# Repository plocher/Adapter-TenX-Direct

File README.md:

# Adapter-TenX-Direct
## License: Creative Commons Attribution-NonCommercial-ShareAlike

Experimental unbuffered I/O expansion board adapter for MRCS cpNode evolution

initial version

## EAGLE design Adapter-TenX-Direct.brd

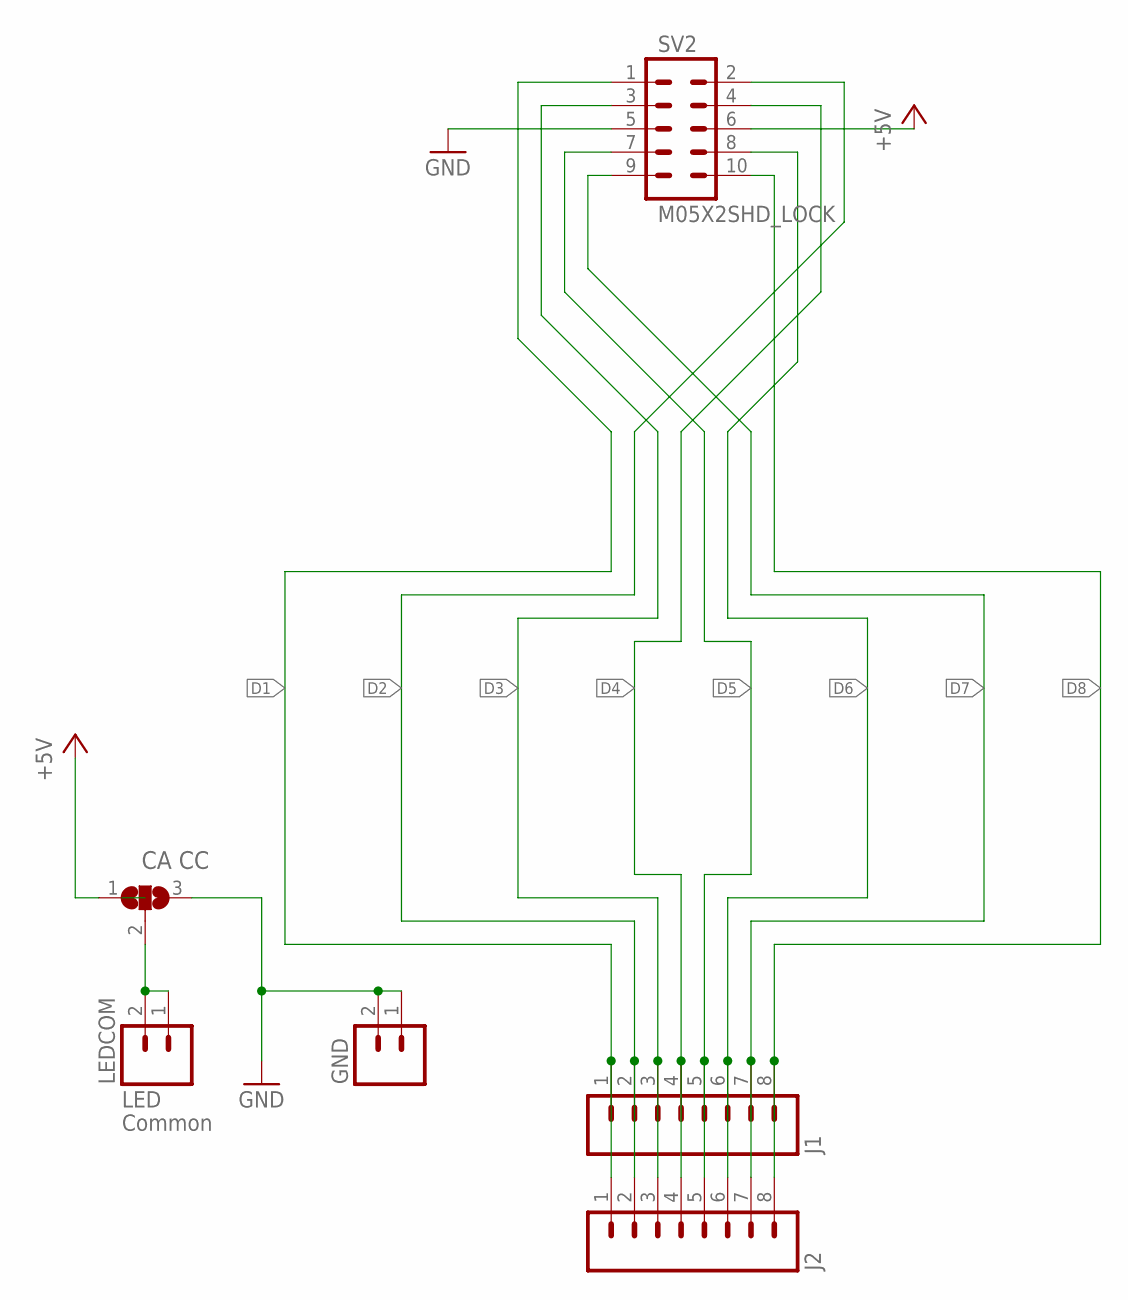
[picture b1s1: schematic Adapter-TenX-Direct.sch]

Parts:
GND: M02POLAR_LOCK; MOLEX-1X2_LOCK
J1: CONNECTOR-M08LOCK_LONGPADS; 1X08_LOCK_LONGPADS
J2: CONNECTOR-M081.56-M; KK-156-8-M
LEDCOM: M02POLAR_LOCK; MOLEX-1X2_LOCK
P1: CA CC; 3P-SMD-2X4.8
SV2: M05X2SHD_LOCK; 2X5-SHROUDED_LOCK

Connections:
+5V: P1.1, SV2.6
D1: J1.1, J2.1, SV2.1
D2: J1.2, J2.2, SV2.2
D3: J1.3, J2.3, SV2.3
D4: J1.4, J2.4, SV2.4
D5: J1.5, J2.5, SV2.7
D6: J1.6, J2.6, SV2.8
D7: J1.7, J2.7, SV2.9
D8: J1.8, J2.8, SV2.10
GND: GND.1, GND.2, P1.3, SV2.5
unnamed: LEDCOM.1, LEDCOM.2, P1.2

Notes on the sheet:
LED
Common

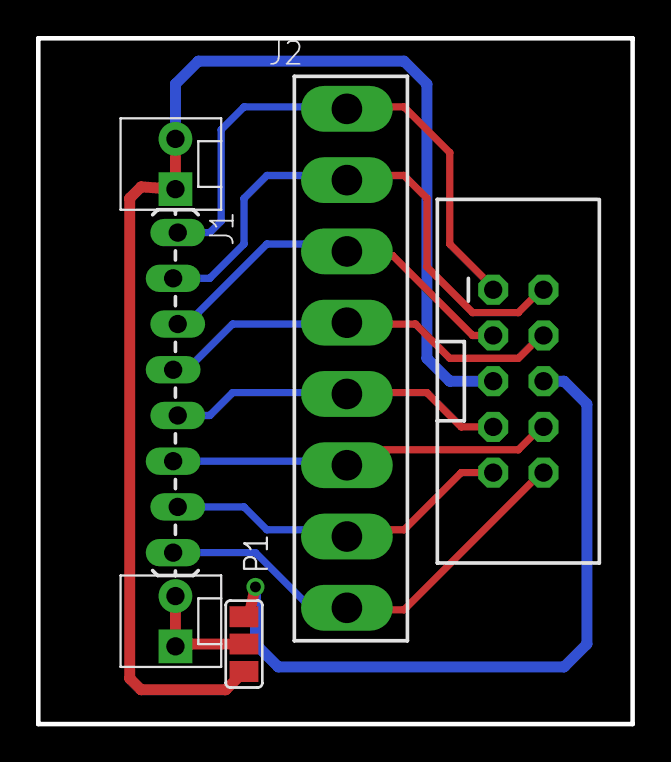
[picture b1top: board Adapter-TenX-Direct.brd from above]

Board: 2 copper layers, 33.0 x 38.1 mm, 6 parts (0 on the bottom side), 11 nets.

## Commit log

2020-05-04 updated tags
